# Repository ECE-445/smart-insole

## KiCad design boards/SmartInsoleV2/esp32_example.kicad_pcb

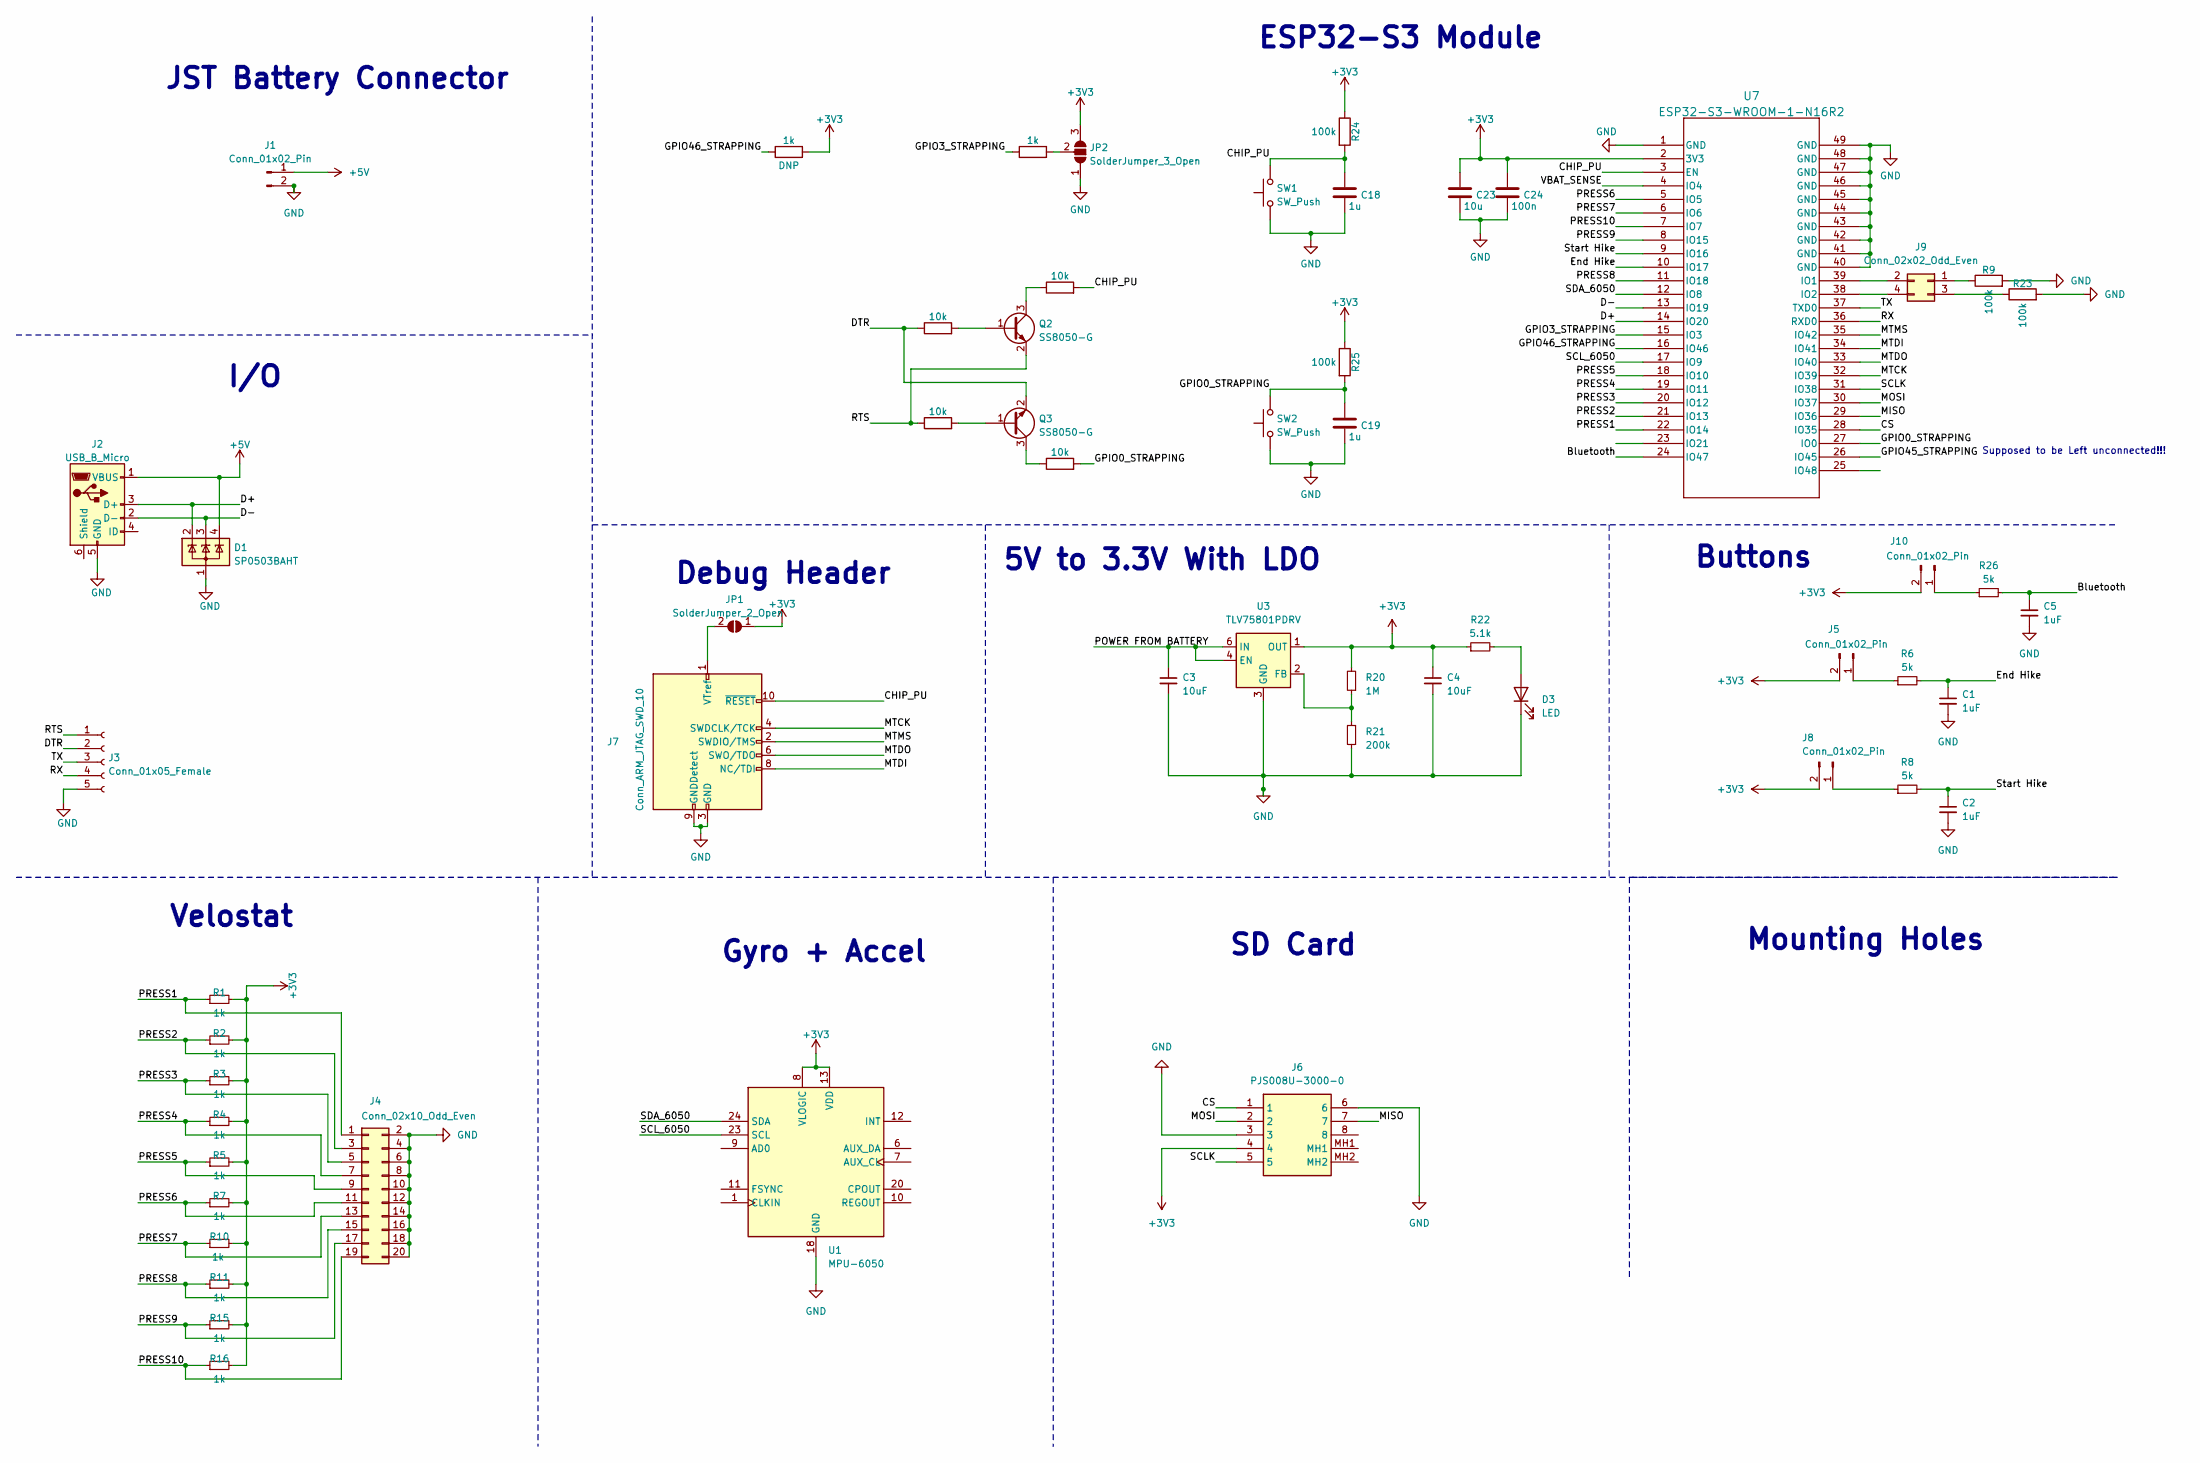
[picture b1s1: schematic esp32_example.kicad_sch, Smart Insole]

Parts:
C1, C2, C5: 1uF; C_0805_2012Metric
C3, C4: 10uF; C_0805_2012Metric
C18, C19: 1u; C_0805_2012Metric
C23: 10u; C_0805_2012Metric
C24: 100n; C_0805_2012Metric
D1: SP0503BAHT; SOT-143
D3: LED; LED_0805_2012Metric
J1: Conn_01x02_Pin; JST_PH_B2B-PH-K_1x02_P2.00mm_Vertical
J2: USB_B_Micro; USB_Micro-B_Amphenol_10118194_Horizontal
J3: Conn_01x05_Female; PinHeader_1x05_P2.54mm_Vertical
J4: Conn_02x10_Odd_Even; PinHeader_2x10_P2.54mm_Vertical
J5, J8, J10: Conn_01x02_Pin; PinHeader_1x02_P2.54mm_Vertical
J6: PJS008U-3000-0; GCT_MEM2051-00-195-00-A; Mouser Part Number 945-PJS008U-3000-0
J7: Conn_ARM_JTAG_SWD_10; IDC-Header_2x05_P2.54mm_Vertical
J9: Conn_02x02_Odd_Even; PinHeader_2x02_P2.54mm_Vertical
JP1: SolderJumper_2_Open; SolderJumper-2_P1.3mm_Open_TrianglePad1.0x1.5mm
JP2: SolderJumper_3_Open; SolderJumper-3_P2.0mm_Open_TrianglePad1.0x1.5mm
Q2, Q3: SS8050-G; SOT-23
R1, R2, R3, R4, R5, R7, R10, R11, R12, R15, R16, R17: 1k; R_0805_2012Metric
R6, R8, R26: 5k; R_0805_2012Metric
R9, R23, R24, R25: 100k; R_0805_2012Metric
R13, R14, R18, R19: 10k; R_0805_2012Metric
R20: 1M; R_0603_1608Metric
R21: 200k; R_0603_1608Metric
R22: 5.1k; R_0603_1608Metric
SW1, SW2: SW_Push; SW_SPST_B3S-1000
U1: MPU-6050; InvenSense_QFN-24_4x4mm_P0.5mm
U3: TLV75801PDRV; WSON-6-1EP_2x2mm_P0.65mm_EP1x1.6mm
U7: ESP32-S3-WROOM-1-N16R2; ESP32-S3-WROOM-1_EXP

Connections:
+3V3: C4.1, C23.1, C24.1, J5.2, J6.4, J8.2, J10.2, JP1.1 (A), JP2.3 (B), R1.2, R2.2, R3.2, R4.2, R5.2, R7.2, R10.2, R11.2, R12.2, R15.2, R16.2, R20.2, R22.1, R24.1, R25.1, U1.8 (VLOGIC), U1.13 (VDD), U3.1 (OUT), U7.2 (3V3)
+5V: D1.4 (K), J1.1, J2.1 (VBUS)
/Bluetooth: C5.1, R26.2, U7.24 (IO47)
/CHIP_PU: C18.1, J7.10 (~RESET), R18.2, R24.2, SW1.2, U7.3 (EN)
/CS: J6.1, U7.28 (IO35)
/D+: D1.2 (K), J2.3 (D+), U7.14 (IO20)
/D-: D1.3 (K), J2.2 (D-), U7.13 (IO19)
/DTR: J3.2, Q3.2 (E), R13.1
/End Hike: C1.1, R6.2, U7.10 (IO17)
/GPIO0_STRAPPING: C19.1, R19.2, R25.2, SW2.2, U7.27 (IO0)
/GPIO3_STRAPPING: R17.1, U7.15 (IO3)
/GPIO45_STRAPPING: U7.26 (IO45)
/GPIO46_STRAPPING: R12.1, U7.16 (IO46)
/MISO: J6.7, U7.29 (IO36)
/MOSI: J6.2, U7.30 (IO37)
/MTCK: J7.4 (SWDCLK/TCK), U7.32 (IO39)
/MTDI: J7.8 (NC/TDI), U7.34 (IO41)
/MTDO: J7.6 (SWO/TDO), U7.33 (IO40)
/MTMS: J7.2 (SWDIO/TMS), U7.35 (IO42)
/POWER FROM BATTERY: C3.1, U3.4 (EN), U3.6 (IN)
/PRESS1: J4.1, R1.1, U7.22 (IO14)
/PRESS2: J4.3, R2.1, U7.21 (IO13)
/PRESS3: J4.5, R3.1, U7.20 (IO12)
/PRESS4: J4.7, R4.1, U7.19 (IO11)
/PRESS5: J4.9, R5.1, U7.18 (IO10)
/PRESS6: J4.11, R7.1, U7.5 (IO5)
/PRESS7: J4.13, R10.1, U7.6 (IO6)
/PRESS8: J4.15, R11.1, U7.11 (IO18)
/PRESS9: J4.17, R15.1, U7.8 (IO15)
/PRESS10: J4.19, R16.1, U7.7 (IO7)
/RTS: J3.1, Q2.2 (E), R14.1
/RX: J3.4, U7.36 (RXD0)
/SCLK: J6.5, U7.31 (IO38)
/SCL_6050: U1.23 (SCL), U7.17 (IO9)
/SDA_6050: U1.24 (SDA), U7.12 (IO8)
/Start Hike: C2.1, R8.2, U7.9 (IO16)
/TX: J3.3, U7.37 (TXD0)
/VBAT_SENSE: U7.4 (IO4)
GND: C1.2, C2.2, C3.2, C4.2, C5.2, C18.2, C19.2, C23.2, C24.2, D1.1 (A), D3.1 (K), J1.2, J2.5 (GND), J3.5, J4.2, J4.4, J4.6, J4.8, J4.10, J4.12, J4.14, J4.16, J4.18, J4.20, J6.3, J6.6, J7.3 (GND), J7.5 (GND), J7.9 (GNDDetect), JP2.1 (A), R9.2, R21.1, R23.2, SW1.1, SW2.1, U1.18 (GND), U3.3 (GND), U3.7 (GND), U7.1 (GND), U7.40 (GND), U7.41 (GND), U7.42 (GND), U7.43 (GND), U7.44 (GND), U7.45 (GND), U7.46 (GND), U7.47 (GND), U7.48 (GND), U7.49 (GND)
unnamed: D3.2 (A), R22.2
unnamed: J5.1, R6.1
unnamed: J7.1 (VTref), JP1.2 (B)
unnamed: J8.1, R8.1
unnamed: J9.1, R9.1
unnamed: J9.2, U7.39 (IO1)
unnamed: J9.3, R23.1
unnamed: J9.4, U7.38 (IO2)
unnamed: J10.1, R26.1
unnamed: JP2.2 (C), R17.2
unnamed: Q2.1 (B), R13.2
unnamed: Q2.3 (C), R18.1
unnamed: Q3.1 (B), R14.2
unnamed: Q3.3 (C), R19.1
unnamed: R20.1, R21.2, U3.2 (FB)

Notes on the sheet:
JST Battery Connector
Buttons
SD Card
Velostat
ESP32-S3 Module
Gyro + Accel
Debug Header
Supposed to be Left unconnected!!!
Mounting Holes
5V to 3.3V With LDO
I/O

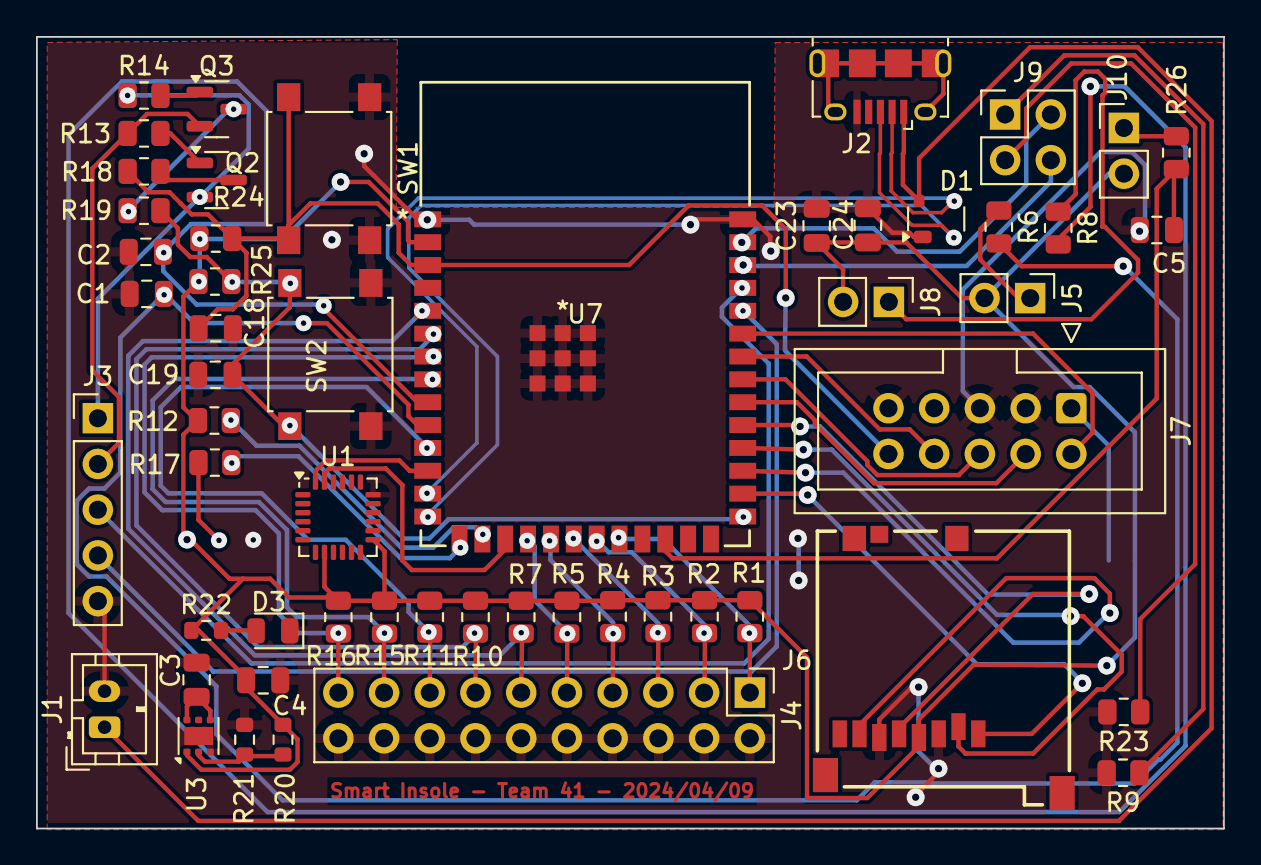
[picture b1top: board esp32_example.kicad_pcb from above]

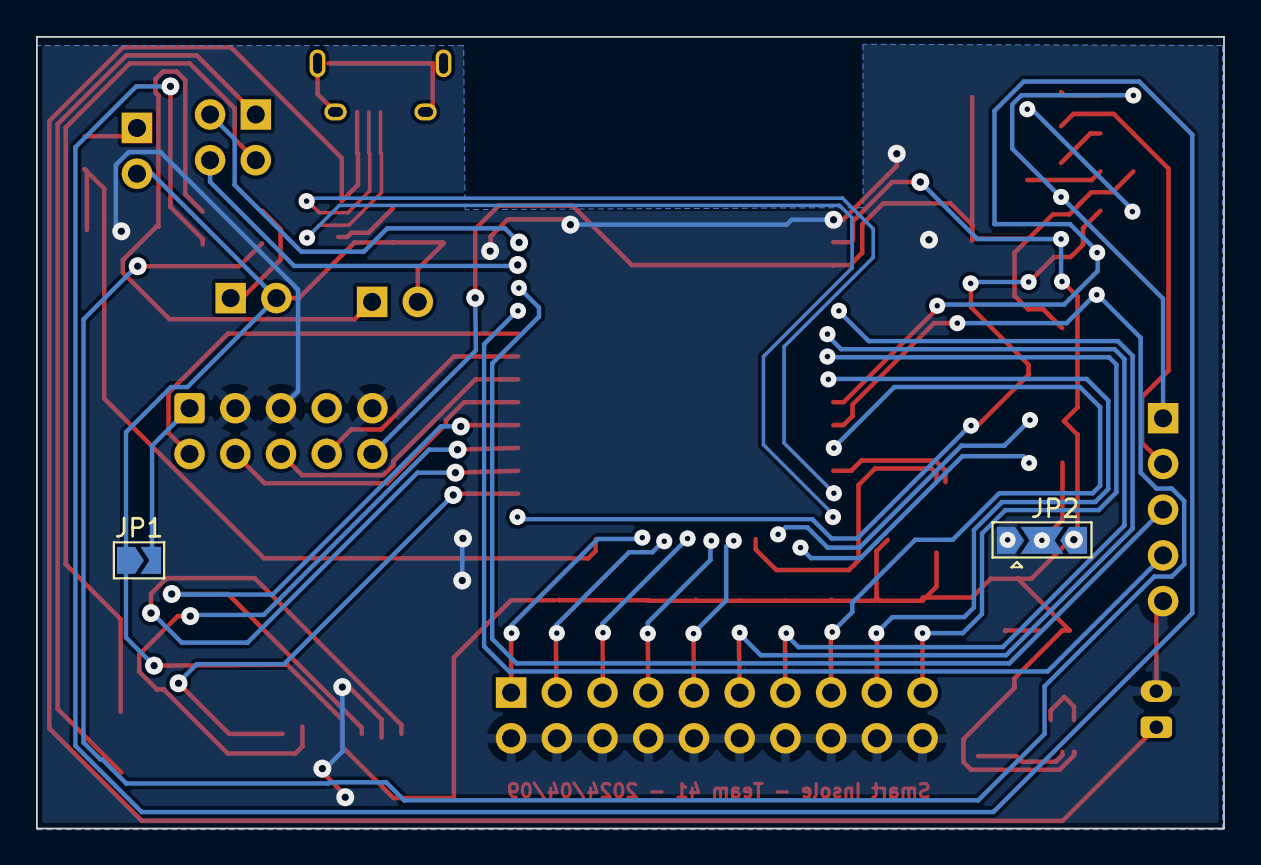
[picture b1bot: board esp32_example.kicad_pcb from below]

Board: 2 copper layers, 65.9 x 44.0 mm, 56 parts (2 on the bottom side), 52 nets.

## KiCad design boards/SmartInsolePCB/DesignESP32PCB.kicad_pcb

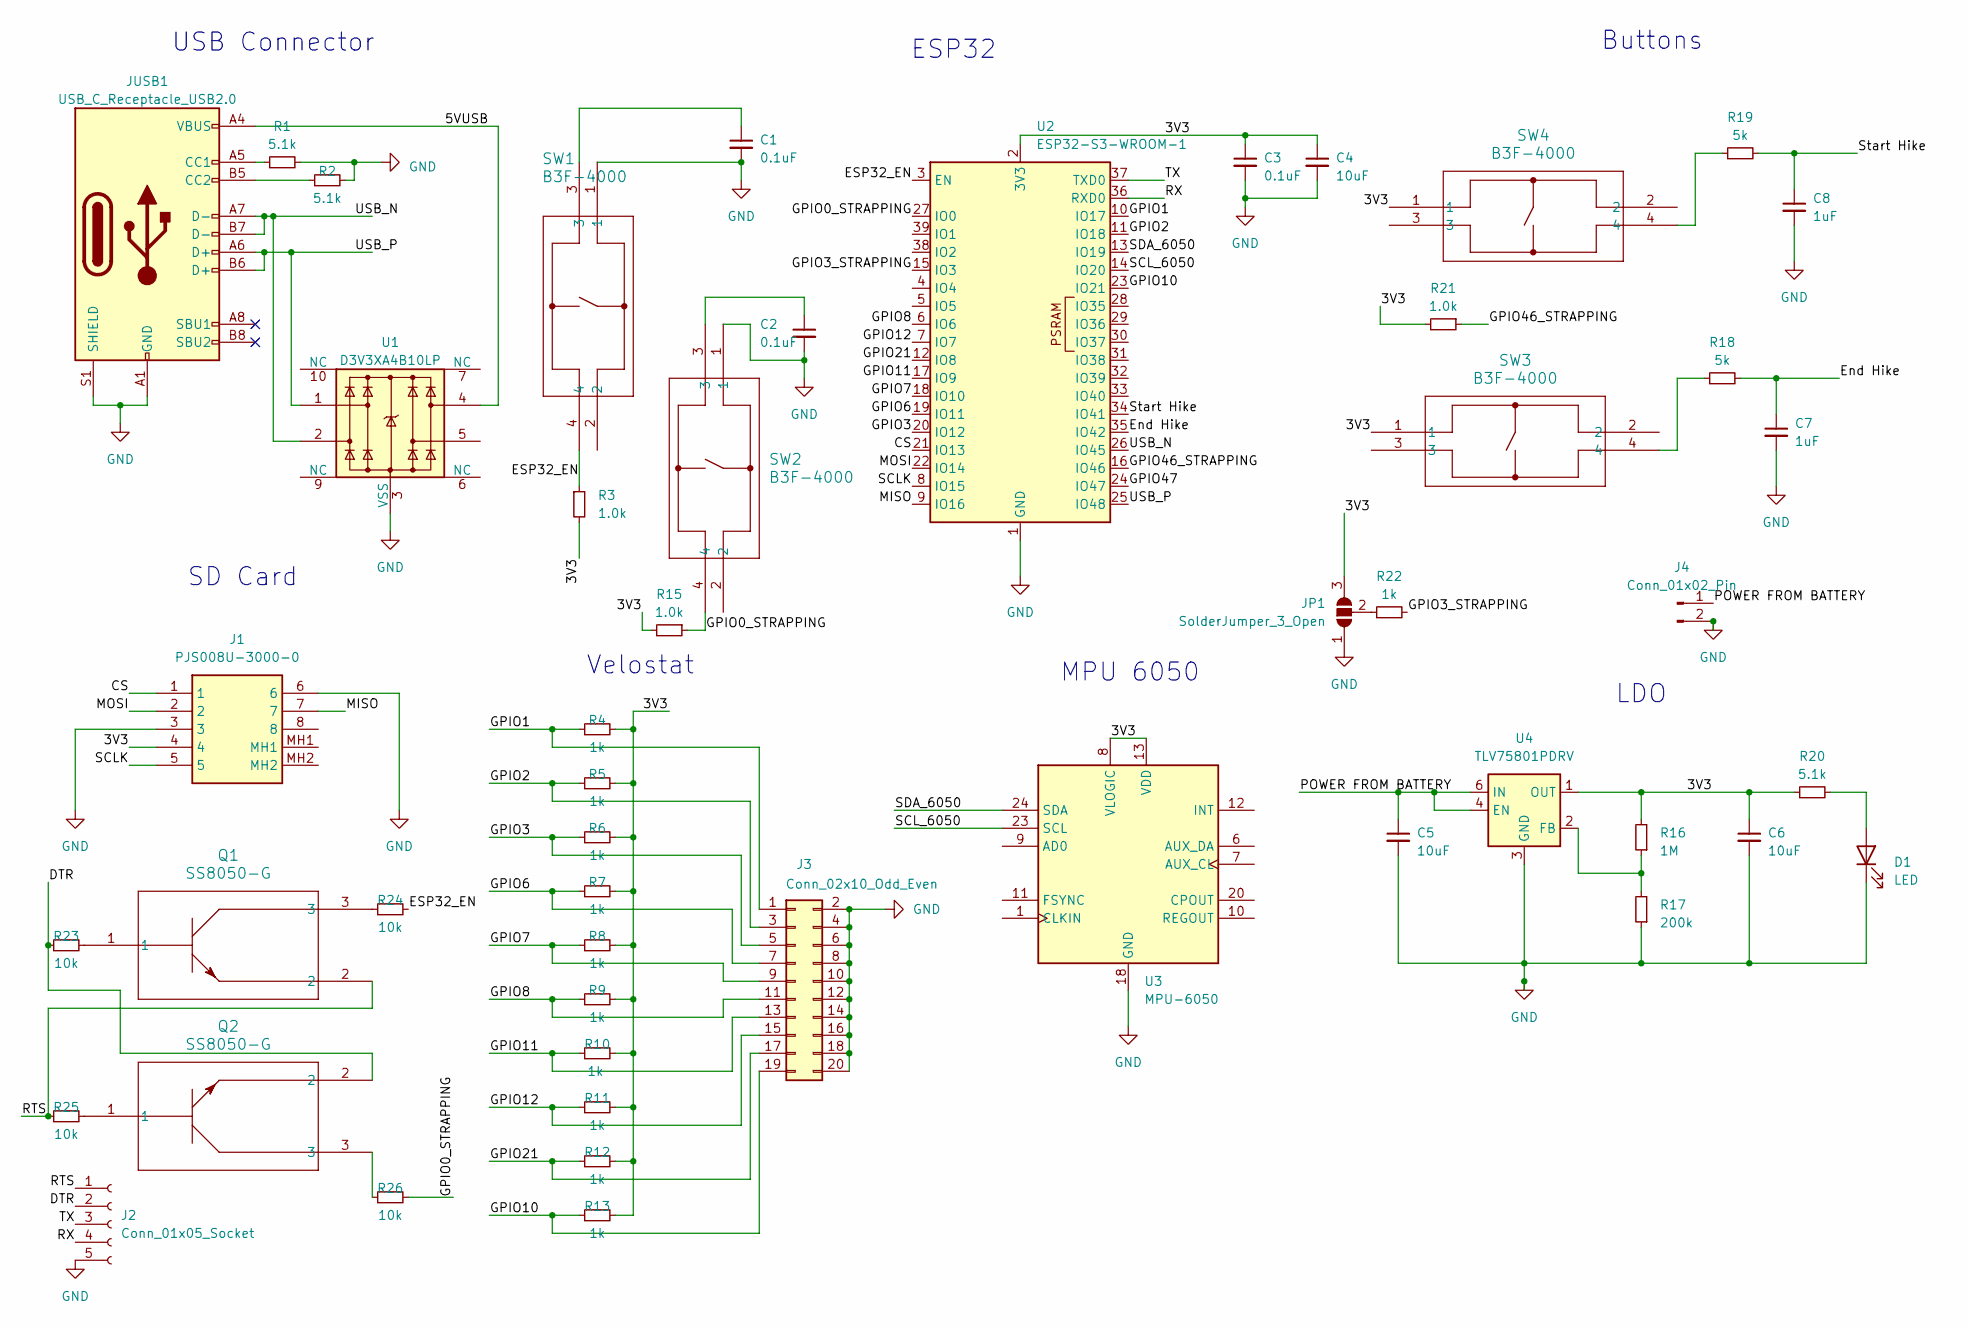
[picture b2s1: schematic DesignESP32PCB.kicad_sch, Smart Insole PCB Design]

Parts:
C1, C2, C3: 0.1uF; C_0603_1608Metric
C4, C5, C6: 10uF; C_0603_1608Metric
C7, C8: 1uF; C_0603_1608Metric
D1: LED; LED_0603_1608Metric
J1: PJS008U-3000-0; PJS008U30000; Mouser Part Number 945-PJS008U-3000-0
J2: Conn_01x05_Socket; PinHeader_1x05_P2.54mm_Vertical
J3: Conn_02x10_Odd_Even; PinHeader_2x10_P2.54mm_Vertical
J4: Conn_01x02_Pin; JST_PH_B2B-PH-K_1x02_P2.00mm_Vertical
JP1: SolderJumper_3_Open; SolderJumper-3_P1.3mm_Open_RoundedPad1.0x1.5mm
JUSB1: USB_C_Receptacle_USB2.0; USB_C_Receptacle_GCT_USB4105-xx-A_16P_TopMnt_Horizontal
Q1, Q2: SS8050-G; TRAN_SS8050-G_CIP
R1, R2, R20: 5.1k; R_0603_1608Metric
R3, R15, R21: 1.0k; R_0603_1608Metric
R4, R5, R6, R7, R8, R9, R10, R11, R12, R13, R22: 1k; R_0603_1608Metric
R16: 1M; R_0603_1608Metric
R17: 200k; R_0603_1608Metric
R18, R19: 5k; R_0603_1608Metric
R23, R24, R25, R26: 10k; R_0603_1608Metric
SW1, SW2, SW3, SW4: B3F-4000; SW_B3F-4000_OMR
U1: D3V3XA4B10LP; Diodes_UDFN-10_1.0x2.5mm_P0.5mm
U2: ESP32-S3-WROOM-1
U3: MPU-6050; InvenSense_QFN-24_4x4mm_P0.5mm
U4: TLV75801PDRV; WSON-6-1EP_2x2mm_P0.65mm_EP1x1.6mm

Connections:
/3V3: C3.1, C4.1, C6.1, J1.4, JP1.3 (B), R3.2, R4.2, R5.2, R6.2, R7.2, R8.2, R9.2, R10.2, R11.2, R12.2, R13.2, R15.2, R16.2, R20.1, R21.2, SW3.1, SW4.1, U2.2 (3V3), U3.8 (VLOGIC), U3.13 (VDD), U4.1 (OUT)
/5VUSB: JUSB1.A4 (VBUS), JUSB1.A9 (VBUS), JUSB1.B4 (VBUS), JUSB1.B9 (VBUS), U1.4
/CS: J1.1, U2.21 (IO13)
/DTR: J2.2, Q2.2, R23.1
/ESP32_EN: R3.1, R24.2, SW1.4, U2.3 (EN)
/End Hike: C7.1, R18.2, U2.35 (IO42)
/GPIO0_STRAPPING: R15.1, R26.2, SW2.4, U2.27 (IO0)
/GPIO1: J3.1, R4.1, U2.10 (IO17)
/GPIO2: J3.3, R5.1, U2.11 (IO18)
/GPIO3: J3.5, R6.1, U2.20 (IO12)
/GPIO3_STRAPPING: R22.2, U2.15 (IO3)
/GPIO6: J3.7, R7.1, U2.19 (IO11)
/GPIO7: J3.9, R8.1, U2.18 (IO10)
/GPIO8: J3.11, R9.1, U2.6 (IO6)
/GPIO10: J3.19, R13.1, U2.23 (IO21)
/GPIO11: J3.13, R10.1, U2.17 (IO9)
/GPIO12: J3.15, R11.1, U2.7 (IO7)
/GPIO21: J3.17, R12.1, U2.12 (IO8)
/GPIO46_STRAPPING: R21.1, U2.16 (IO46)
/GPIO47: U2.24 (IO47)
/MISO: J1.7, U2.9 (IO16)
/MOSI: J1.2, U2.22 (IO14)
/POWER FROM BATTERY: C5.1, J4.1, U4.4 (EN), U4.6 (IN)
/RTS: J2.1, Q1.2, R25.1
/RX: J2.4, U2.36 (RXD0)
/SCLK: J1.5, U2.8 (IO15)
/SCL_6050: U2.14 (IO20), U3.23 (SCL)
/SDA_6050: U2.13 (IO19), U3.24 (SDA)
/Start Hike: C8.1, R19.2, U2.34 (IO41)
/TX: J2.3, U2.37 (TXD0)
/USB_N: JUSB1.A7 (D-), JUSB1.B7 (D-), U1.2, U2.26 (IO45)
/USB_P: JUSB1.A6 (D+), JUSB1.B6 (D+), U1.1, U2.25 (IO48)
GND: C1.2, C2.2, C3.2, C4.2, C5.2, C6.2, C7.2, C8.2, D1.1 (K), J1.3, J1.6, J2.5, J3.2, J3.4, J3.6, J3.8, J3.10, J3.12, J3.14, J3.16, J3.18, J3.20, J4.2, JP1.1 (A), JUSB1.A1 (GND), JUSB1.A12 (GND), JUSB1.B1 (GND), JUSB1.B12 (GND), JUSB1.S1 (SHIELD), R1.2, R2.2, R17.1, SW1.1, SW2.1, U1.3 (VSS), U1.8 (VSS), U2.1 (GND), U2.40 (GND), U2.41 (GND), U3.18 (GND), U4.3 (GND), U4.7 (GND)
unnamed: C1.1, SW1.3
unnamed: C2.1, SW2.3
unnamed: D1.2 (A), R20.2
unnamed: JP1.2 (C), R22.1
unnamed: JUSB1.A5 (CC1), R1.1
unnamed: JUSB1.B5 (CC2), R2.1
unnamed: Q1.1, R23.2
unnamed: Q1.3, R24.1
unnamed: Q2.1, R25.2
unnamed: Q2.3, R26.1
unnamed: R18.1, SW3.4
unnamed: R19.1, SW4.4
unnamed: R16.1, R17.2, U4.2 (FB)

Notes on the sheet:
MPU 6050
ESP32
SD Card
USB Connector
LDO
Buttons
Velostat

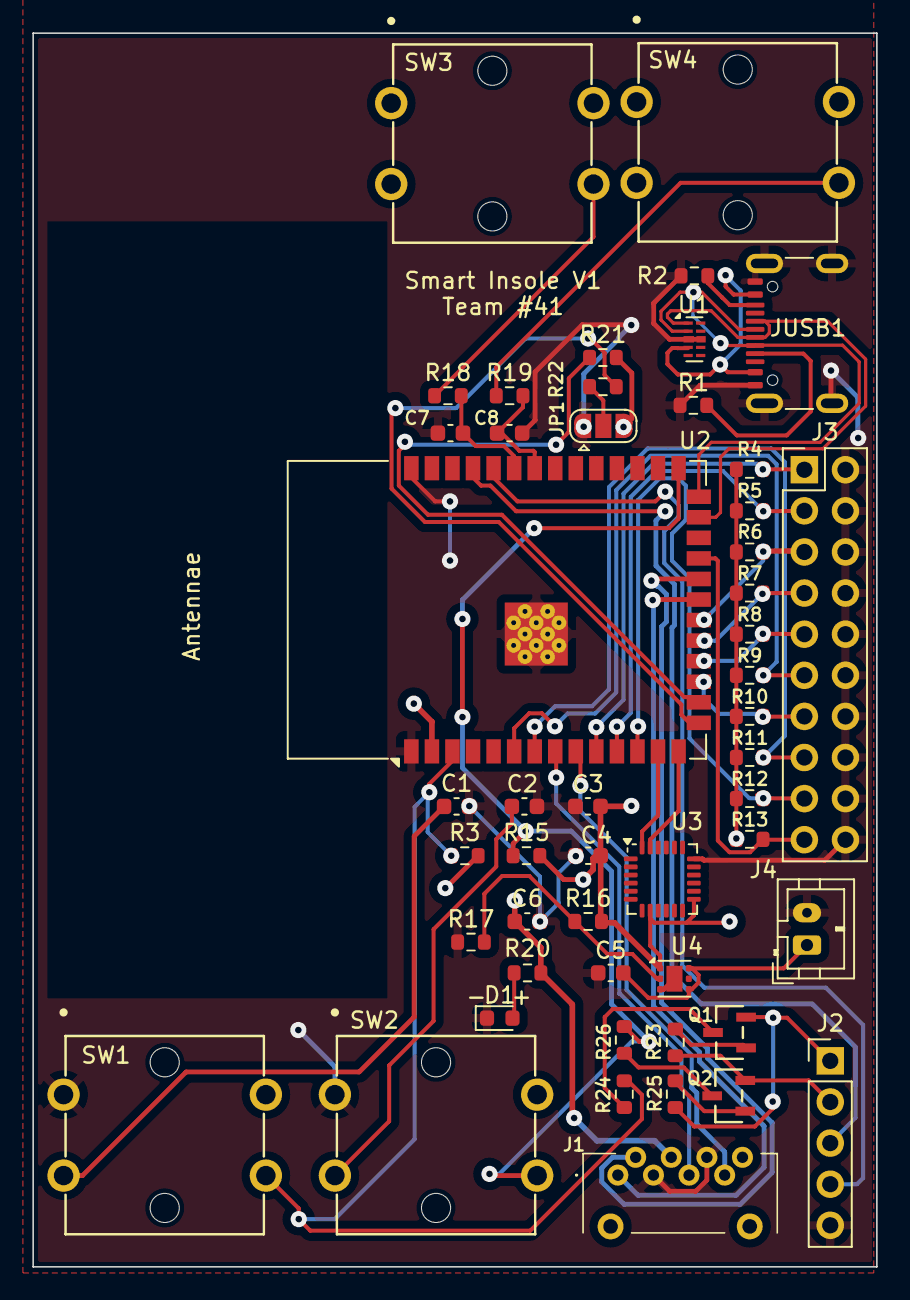
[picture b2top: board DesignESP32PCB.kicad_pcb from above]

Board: 2 copper layers, 52.1 x 76.2 mm, 50 parts (0 on the bottom side), 45 nets.

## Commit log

2024-02-05 innital setup
2024-02-05 init to example project
2024-02-05 added rest of folders
2024-02-29 addedc notebook entries
2024-02-29 Gitnore
2024-02-29 Project With basic layout
2024-03-01 added 6050, added footprints
2024-03-01 added SD card Pin headers
2024-03-01 replaced ESP32 symbol
2024-03-01 PCB design
2024-03-04 debounced buttons and connected pins
2024-03-05 finished schematic
2024-03-05 finished all PCB connections
2024-03-05 finished PCB second push just in case
2024-03-05 changed GPIO
2024-03-05 down from 200 to 43 errors
2024-03-06 schematic and pcb updates
2024-03-18 put extra comp on board
2024-03-18 down to 56
2024-03-18 2 missing connections and 16 erros
2024-03-19 saved work
2024-03-19 added footprint
2024-03-19 routed all connections
2024-03-19 extra commits
2024-03-19 3/19 update
2024-03-19 Passed checks and gerber file created
2024-03-19 quick changes
2024-03-25 React App Init
2024-03-29 Added notebooks/code
2024-03-31 added initial heatmap
2024-03-31 Added chart to main page
2024-03-31 Comment for more chart examples
2024-04-01 Notebook update
2024-04-01 updated heatmap
2024-04-02 router and bluetooth with esp 32
2024-04-02 updating notebook
2024-04-04 board V2
2024-04-04 a little progress
2024-04-05 Most of routing done
2024-04-05 updated peripheral/accel code
2024-04-06 fixed a few more errors
2024-04-06 latest
2024-04-06 added changes but not finished
2024-04-09 re made board
2024-04-09 7 fine errors but need to double check the SD card footprint
2024-04-09 all errors checked including place from schematic
2024-04-10 submitted for round 5
2024-04-10 added dimensions
2024-04-10 Updated lab notbook
2024-04-10 update lab notebook
2024-04-10 Spell check on goolge docs
2024-04-25 Dimensions on PCB + notebook update
2024-04-29 Lab notebook update
2024-04-29 Spelling
2024-04-29 fix broken figure
2024-05-01 uploading everything
2024-05-02 Final Notebook Update
2024-05-02 Notebook in other format
2024-05-02 added to readme.md
